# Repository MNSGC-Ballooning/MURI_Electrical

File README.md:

# MURI_Electric
Repository containing EAGLE schematics and PCB files for MURI related payloads

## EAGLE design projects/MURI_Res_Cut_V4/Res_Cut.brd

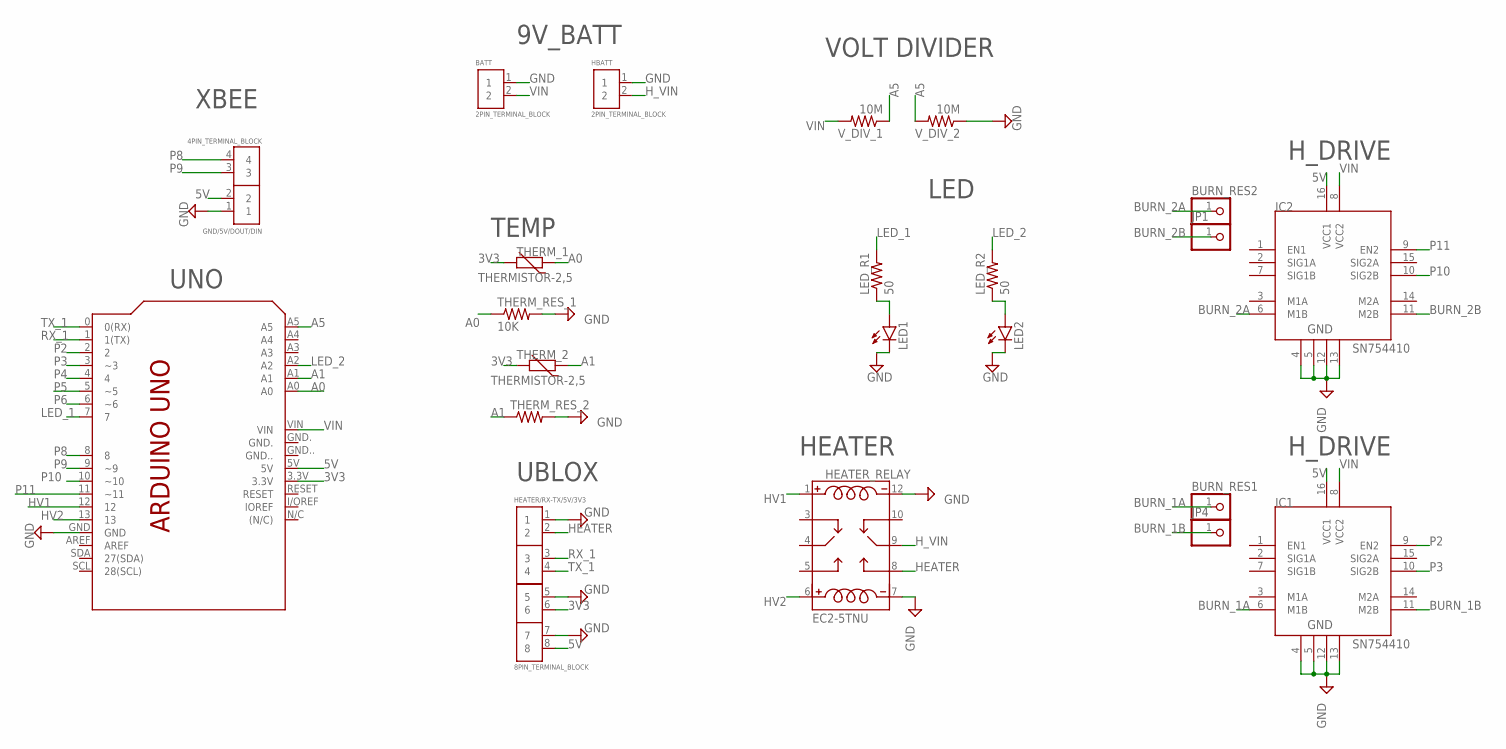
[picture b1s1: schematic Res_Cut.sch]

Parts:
BATT: 2PIN_TERMINAL_BLOCK
BURN_RES1, BURN_RES2: PINHD-1X1CB; 1X01-CLEANBIG
GND/5V/DOUT/DIN: 4PIN_TERMINAL_BLOCK
HBATT: 2PIN_TERMINAL_BLOCK
HEATER/RX-TX/5V/3V3: 8PIN_TERMINAL_BLOCK
HEATER_RELAY: EC2-5TNU; RELAY_EC2-5TNU
IC1, IC2: SN754410; DIP16
JP1, JP4: PINHD-1X1CB; 1X01-CLEANBIG
LED1, LED2: TLLR4400; LED3MM
LED_R1, LED_R2: 50; 0204/7
PCB1: ARDUINO_UNO
THERM_1, THERM_2: THERMISTOR-2,5; RS-2,5
THERM_RES_1, THERM_RES_2: 10K; 0204/7
V_DIV_1, V_DIV_2: 10M; 0204/7

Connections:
3V3: HEATER/RX-TX/5V/3V3.6, PCB1.3.3V, THERM_1.2, THERM_2.2
5V: GND/5V/DOUT/DIN.2, HEATER/RX-TX/5V/3V3.8, IC1.16 (VCC1), IC2.16 (VCC1), PCB1.5V
A0: PCB1.A0, THERM_1.1, THERM_RES_1.1
A1: PCB1.A1, THERM_2.1, THERM_RES_2.1
A5: PCB1.A5, V_DIV_1.1, V_DIV_2.2
BLUE_R2: LED2.A, LED_R2.1
BURN_1A: BURN_RES1.1, IC1.6 (M1B)
BURN_1B: IC1.11 (M2B), JP4.1
BURN_2A: BURN_RES2.1, IC2.6 (M1B)
BURN_2B: IC2.11 (M2B), JP1.1
GND: BATT.1, GND/5V/DOUT/DIN.1, HBATT.1, HEATER/RX-TX/5V/3V3.1, HEATER/RX-TX/5V/3V3.5, HEATER/RX-TX/5V/3V3.7, HEATER_RELAY.7 (C4), HEATER_RELAY.12 (C2), IC1.4, IC1.5, IC1.12, IC1.13, IC2.4, IC2.5, IC2.12, IC2.13, LED1.K (C), LED2.K (C), PCB1.GND, THERM_RES_1.2, THERM_RES_2.2, V_DIV_2.1
HEATER: HEATER/RX-TX/5V/3V3.2, HEATER_RELAY.8 (NO)
HV1: HEATER_RELAY.1 (C1), PCB1.12
HV2: HEATER_RELAY.6 (C3), PCB1.13
H_VIN: HBATT.2, HEATER_RELAY.9 (M)
LED_1: LED_R1.2, PCB1.7
LED_2: LED_R2.2, PCB1.A2
unnamed: LED1.A, LED_R1.1
P2: IC1.9 (EN2), PCB1.2
P3: IC1.10 (SIG2B), PCB1.3 (~3)
P4: PCB1.4
P5: PCB1.5 (~5)
P6: PCB1.6 (~6)
P8: GND/5V/DOUT/DIN.4, PCB1.8
P9: GND/5V/DOUT/DIN.3, PCB1.9 (~9)
P10: IC2.10 (SIG2B), PCB1.10 (~10)
P11: IC2.9 (EN2), PCB1.11 (~11)
RX_1: HEATER/RX-TX/5V/3V3.3, PCB1.1 (1(TX))
TX_1: HEATER/RX-TX/5V/3V3.4, PCB1.0 (0(RX))
VIN: BATT.2, IC1.8 (VCC2), IC2.8 (VCC2), PCB1.VIN, V_DIV_1.2

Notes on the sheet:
TEMP
HEATER
H_DRIVE
UBLOX
XBEE
9V_BATT
UNO
LED
VOLT DIVIDER

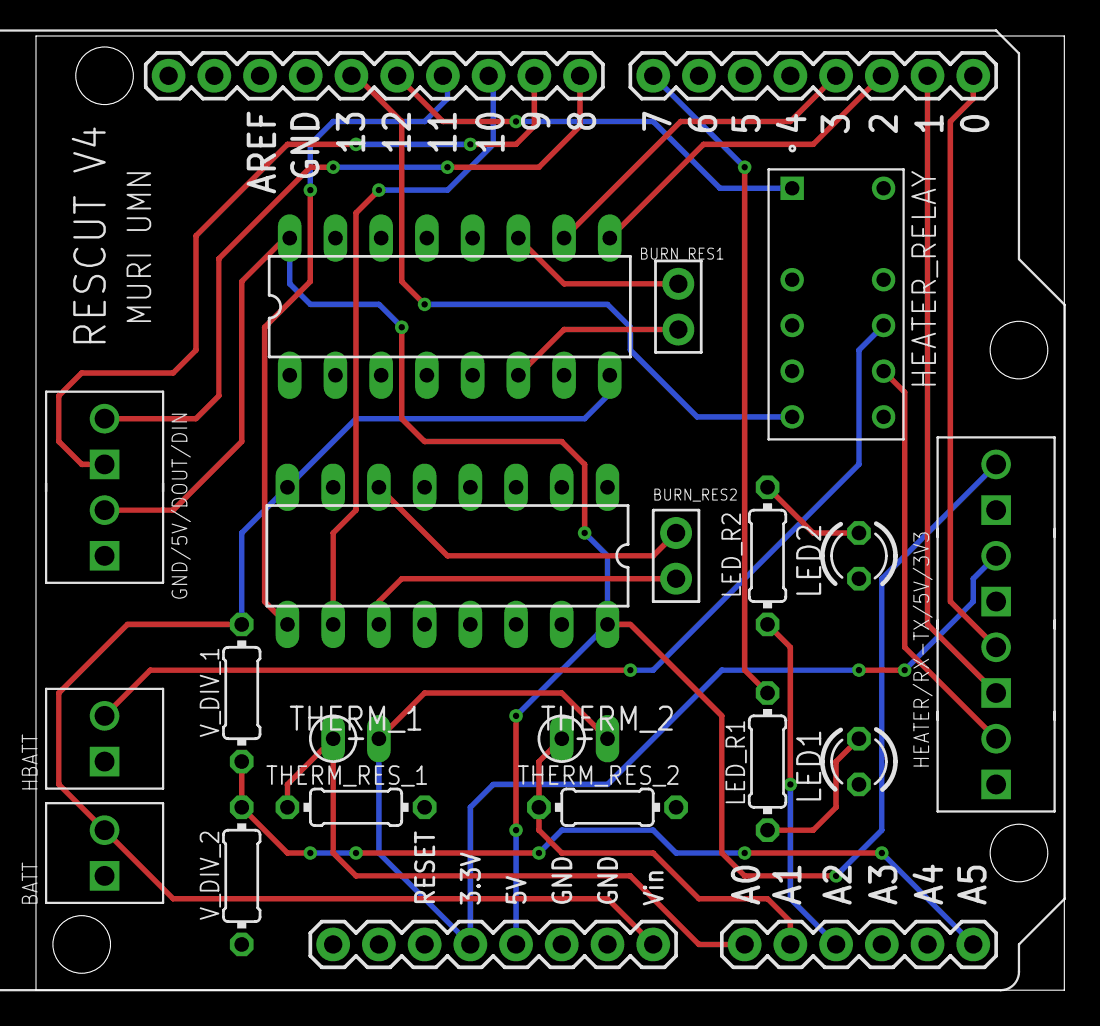
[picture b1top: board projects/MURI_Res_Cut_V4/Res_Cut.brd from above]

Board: 2 copper layers, 57.1 x 53.0 mm, 22 parts (0 on the bottom side), 27 nets.

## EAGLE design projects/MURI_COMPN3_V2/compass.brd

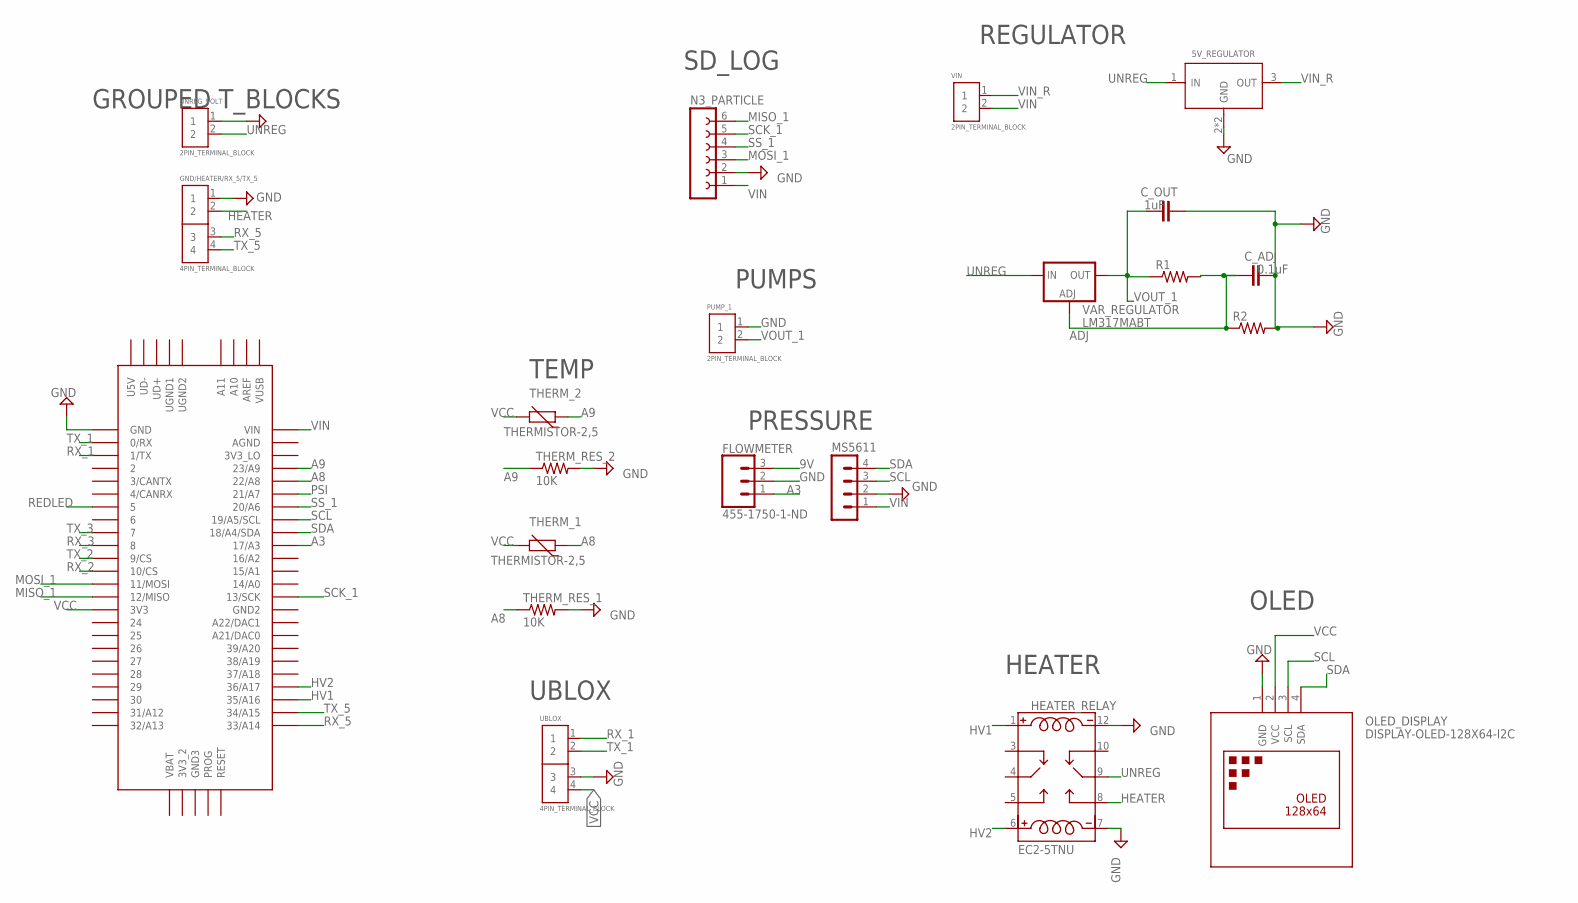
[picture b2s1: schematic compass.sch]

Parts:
5V_REGULATOR: PMIC-L7805CV-DG(TO-220); TO-220
C_ADJ: 0.1uF; C2.5-3
C_OUT: 1uF; C2.5-3
FLOWMETER: 455-1750-1-ND; 1X03
GND/HEATER/RX_5/TX_5: 4PIN_TERMINAL_BLOCK
HEATER_RELAY: EC2-5TNU; RELAY_EC2-5TNU
MS5611: MA04-1
N3_PARTICLE: FE06-1; FE06
OLED_DISPLAY: DISPLAY-OLED-128X64-I2C
PUMP_1: 2PIN_TERMINAL_BLOCK
R1, R2: 0204/7
THERM_1, THERM_2: THERMISTOR-2,5; RS-2,5
THERM_RES_1, THERM_RES_2: 10K; 0204/7
U$1: TEENSY_3.5/3.6
UBLOX: 4PIN_TERMINAL_BLOCK
UNREG_VOLT: 2PIN_TERMINAL_BLOCK
VAR_REGULATOR: LM317MABT; TO220L1
VIN: 2PIN_TERMINAL_BLOCK

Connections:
9V: FLOWMETER.3
A3: FLOWMETER.1, U$1.17/A3
A8: THERM_1.1, THERM_RES_1.1, U$1.22/A8
A9: THERM_2.1, THERM_RES_2.1, U$1.23/A9
ADJ: C_ADJ.2, R1.2, R2.1, VAR_REGULATOR.1 (ADJ)
GND: 5V_REGULATOR.2 (GND), 5V_REGULATOR.HEAT (GND), C_ADJ.1, C_OUT.2, FLOWMETER.2, GND/HEATER/RX_5/TX_5.1, HEATER_RELAY.7 (C4), HEATER_RELAY.12 (C2), MS5611.2, N3_PARTICLE.2, OLED_DISPLAY.1 (GND), PUMP_1.1, R2.2, THERM_RES_1.2, THERM_RES_2.2, U$1.GND, UBLOX.3, UNREG_VOLT.1
HEATER: GND/HEATER/RX_5/TX_5.2, HEATER_RELAY.8 (NO)
HV1: HEATER_RELAY.1 (C1), U$1.35/A16
HV2: HEATER_RELAY.6 (C3), U$1.36/A17
MISO_1: N3_PARTICLE.6, U$1.12/MISO
MOSI_1: N3_PARTICLE.3, U$1.11/MOSI
PSI: U$1.21/A7
REDLED: U$1.5
RX_1: U$1.1/TX, UBLOX.1
RX_2: U$1.10/CS
RX_3: U$1.8
RX_5: GND/HEATER/RX_5/TX_5.3, U$1.33/A14
SCK_1: N3_PARTICLE.5, U$1.13/SCK
SCL: MS5611.3, OLED_DISPLAY.3 (SCL), U$1.19/A5/SCL
SDA: MS5611.4, OLED_DISPLAY.4 (SDA), U$1.18/A4/SDA
SS_1: N3_PARTICLE.4, U$1.20/A6
TX_1: U$1.0/RX, UBLOX.2
TX_2: U$1.9/CS
TX_3: U$1.7
TX_5: GND/HEATER/RX_5/TX_5.4, U$1.34/A15
UNREG: 5V_REGULATOR.1 (IN), HEATER_RELAY.9 (M), UNREG_VOLT.2, VAR_REGULATOR.3 (IN)
VCC: OLED_DISPLAY.2 (VCC), THERM_1.2, THERM_2.2, U$1.3V3, UBLOX.4
VIN: MS5611.1, N3_PARTICLE.1, U$1.VIN, VIN.2
VIN_R: 5V_REGULATOR.3 (OUT), VIN.1
VOUT_1: C_OUT.1, PUMP_1.2, R1.1, VAR_REGULATOR.2 (OUT)

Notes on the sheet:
UBLOX
PRESSURE
OLED
PUMPS
HEATER
REGULATOR
SD_LOG
TEMP
GROUPED T_BLOCKS

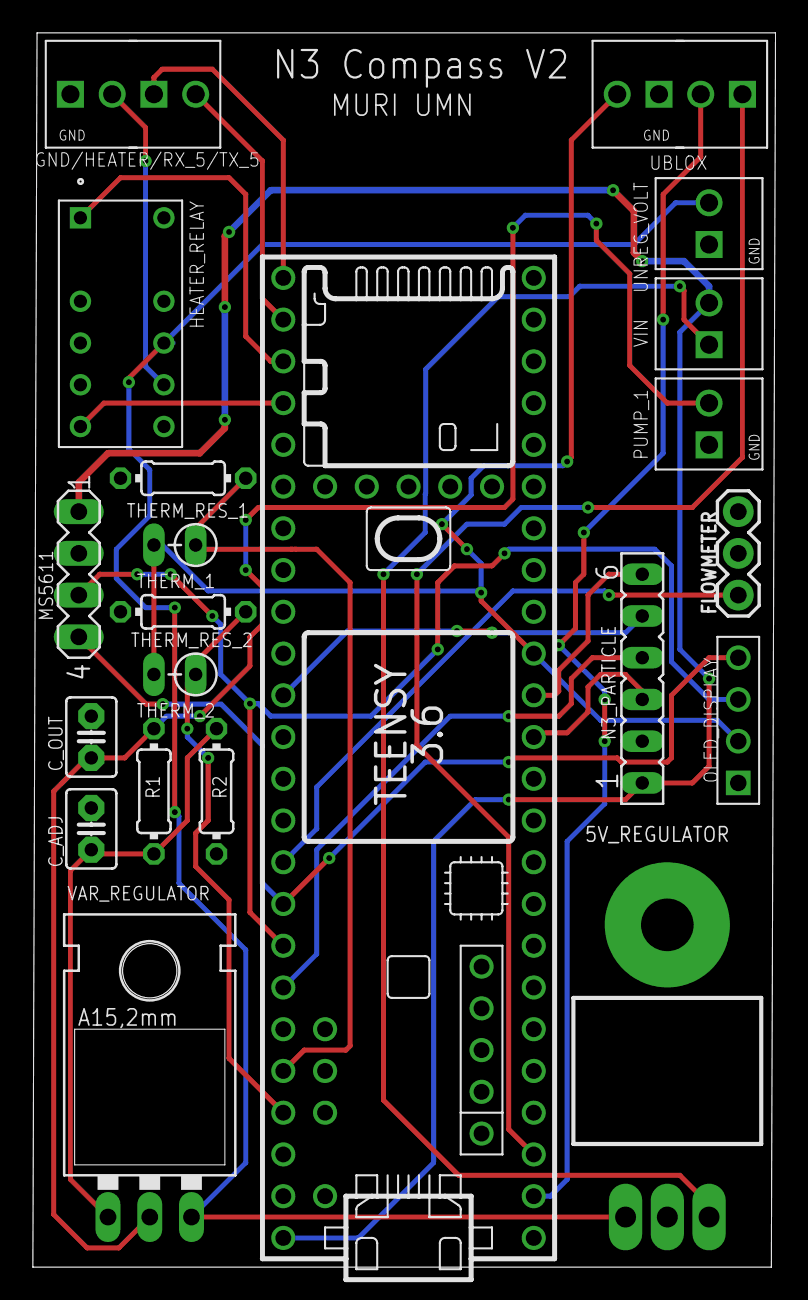
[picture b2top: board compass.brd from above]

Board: 2 copper layers, 45.2 x 75.1 mm, 21 parts (0 on the bottom side), 23 nets.

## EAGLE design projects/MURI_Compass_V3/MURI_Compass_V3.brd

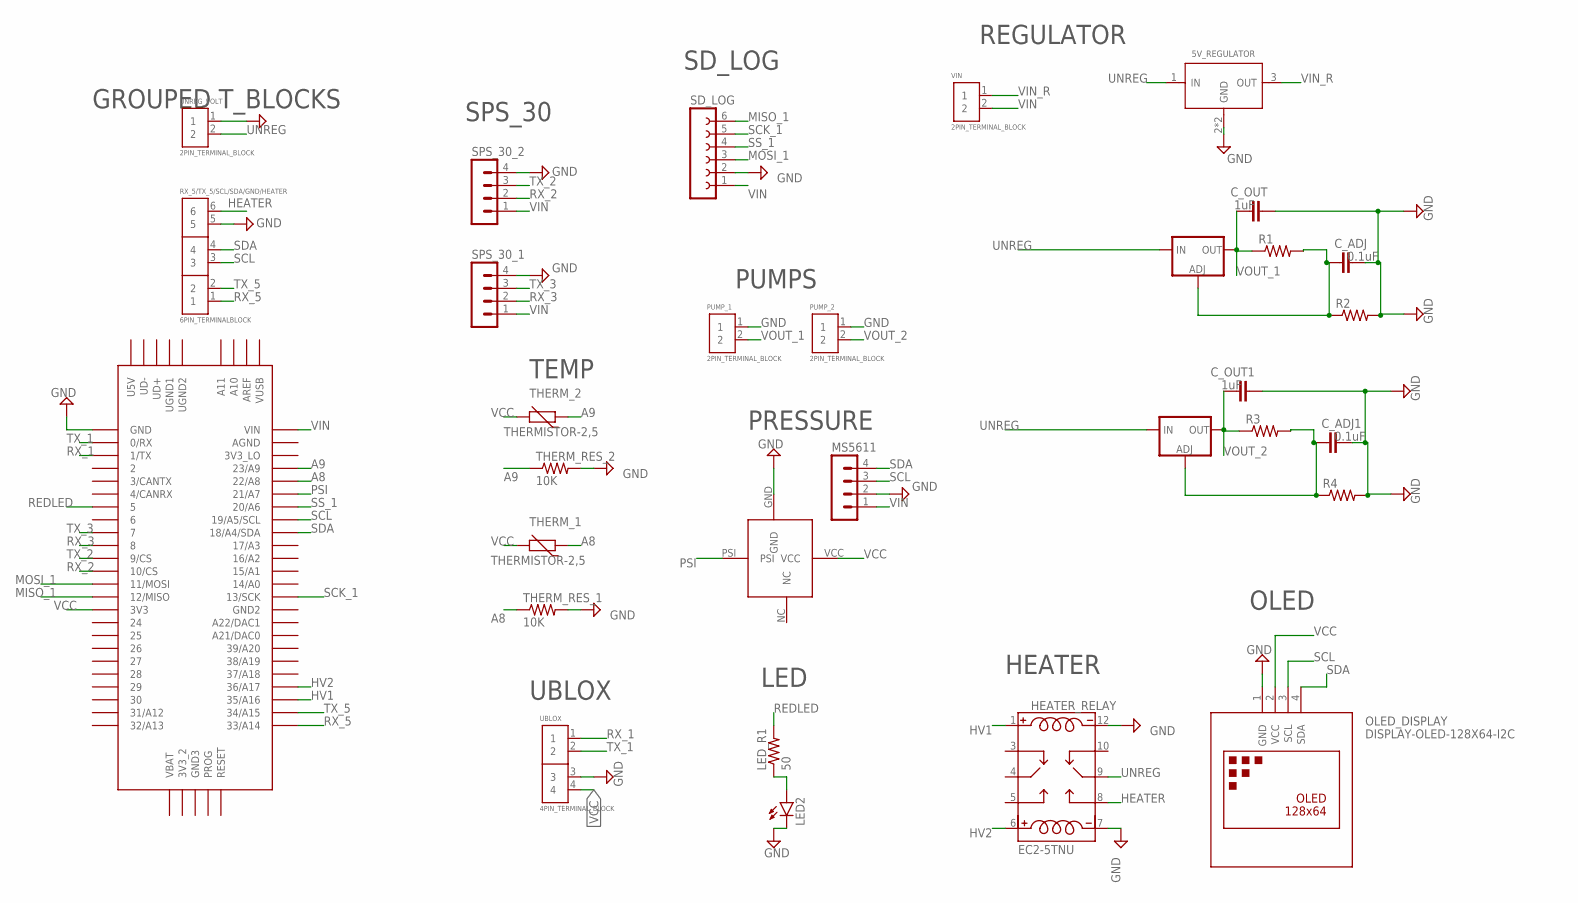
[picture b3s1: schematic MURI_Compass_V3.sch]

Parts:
5V_REGULATOR: PMIC-L7805CV-DG(TO-220); TO-220
C_ADJ, C_ADJ1: 0.1uF; C2.5-3
C_OUT, C_OUT1: 1uF; C2.5-3
HEATER_RELAY: EC2-5TNU; RELAY_EC2-5TNU
LED2: TLLR4400; LED3MM
LED_R1: 50; 0204/7
MS5611: MA04-1
OLED_DISPLAY: DISPLAY-OLED-128X64-I2C
PRESSURE_SENSOR: SSCSANN015PAAA5
PUMP_1, PUMP_2: 2PIN_TERMINAL_BLOCK
R1, R2, R3, R4: 0204/7
RX_5/TX_5/SCL/SDA/GND/HEATER: 6PIN_TERMINALBLOCK
SD_LOG: FE06-1; FE06
SPS_30_1, SPS_30_2: MA04-1
THERM_1, THERM_2: THERMISTOR-2,5; RS-2,5
THERM_RES_1, THERM_RES_2: 10K; 0204/7
U1, U2: V_REG_317SINK; TO220-ADJ
U$1: TEENSY_3.5/3.6
UBLOX: 4PIN_TERMINAL_BLOCK
UNREG_VOLT: 2PIN_TERMINAL_BLOCK
VIN: 2PIN_TERMINAL_BLOCK

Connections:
A8: THERM_1.1, THERM_RES_1.1, U$1.22/A8
A9: THERM_2.1, THERM_RES_2.1, U$1.23/A9
GND: 5V_REGULATOR.2 (GND), 5V_REGULATOR.HEAT (GND), C_ADJ.1, C_ADJ1.1, C_OUT.2, C_OUT1.2, HEATER_RELAY.7 (C4), HEATER_RELAY.12 (C2), LED2.K (C), MS5611.2, OLED_DISPLAY.1 (GND), PRESSURE_SENSOR.GND, PUMP_1.1, PUMP_2.1, R2.2, R4.2, RX_5/TX_5/SCL/SDA/GND/HEATER.5, SD_LOG.2, SPS_30_1.4, SPS_30_2.4, THERM_RES_1.2, THERM_RES_2.2, U$1.GND, UBLOX.3, UNREG_VOLT.1
HEATER: HEATER_RELAY.8 (NO), RX_5/TX_5/SCL/SDA/GND/HEATER.6
HV1: HEATER_RELAY.1 (C1), U$1.35/A16
HV2: HEATER_RELAY.6 (C3), U$1.36/A17
MISO_1: SD_LOG.6, U$1.12/MISO
MOSI_1: SD_LOG.3, U$1.11/MOSI
unnamed: C_ADJ1.2, R3.2, R4.1, U2.ADJ
unnamed: LED2.A, LED_R1.1
unnamed: C_ADJ.2, R1.2, R2.1, U1.ADJ
PSI: PRESSURE_SENSOR.PSI, U$1.21/A7
REDLED: LED_R1.2, U$1.5
RX_1: U$1.1/TX, UBLOX.1
RX_2: SPS_30_2.2, U$1.10/CS
RX_3: SPS_30_1.2, U$1.8
RX_5: RX_5/TX_5/SCL/SDA/GND/HEATER.1, U$1.33/A14
SCK_1: SD_LOG.5, U$1.13/SCK
SCL: MS5611.3, OLED_DISPLAY.3 (SCL), RX_5/TX_5/SCL/SDA/GND/HEATER.3, U$1.19/A5/SCL
SDA: MS5611.4, OLED_DISPLAY.4 (SDA), RX_5/TX_5/SCL/SDA/GND/HEATER.4, U$1.18/A4/SDA
SS_1: SD_LOG.4, U$1.20/A6
TX_1: U$1.0/RX, UBLOX.2
TX_2: SPS_30_2.3, U$1.9/CS
TX_3: SPS_30_1.3, U$1.7
TX_5: RX_5/TX_5/SCL/SDA/GND/HEATER.2, U$1.34/A15
UNREG: 5V_REGULATOR.1 (IN), HEATER_RELAY.9 (M), U1.IN, U2.IN, UNREG_VOLT.2
VCC: OLED_DISPLAY.2 (VCC), PRESSURE_SENSOR.VCC, THERM_1.2, THERM_2.2, U$1.3V3, UBLOX.4
VIN: MS5611.1, SD_LOG.1, SPS_30_1.1, SPS_30_2.1, U$1.VIN, VIN.2
VIN_R: 5V_REGULATOR.3 (OUT), VIN.1
VOUT_1: C_OUT.1, PUMP_1.2, R1.1, U1.OUT
VOUT_2: C_OUT1.1, PUMP_2.2, R3.1, U2.OUT

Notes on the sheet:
UBLOX
LED
PRESSURE
OLED
PUMPS
HEATER
REGULATOR
SD_LOG
SPS_30
TEMP
GROUPED T_BLOCKS

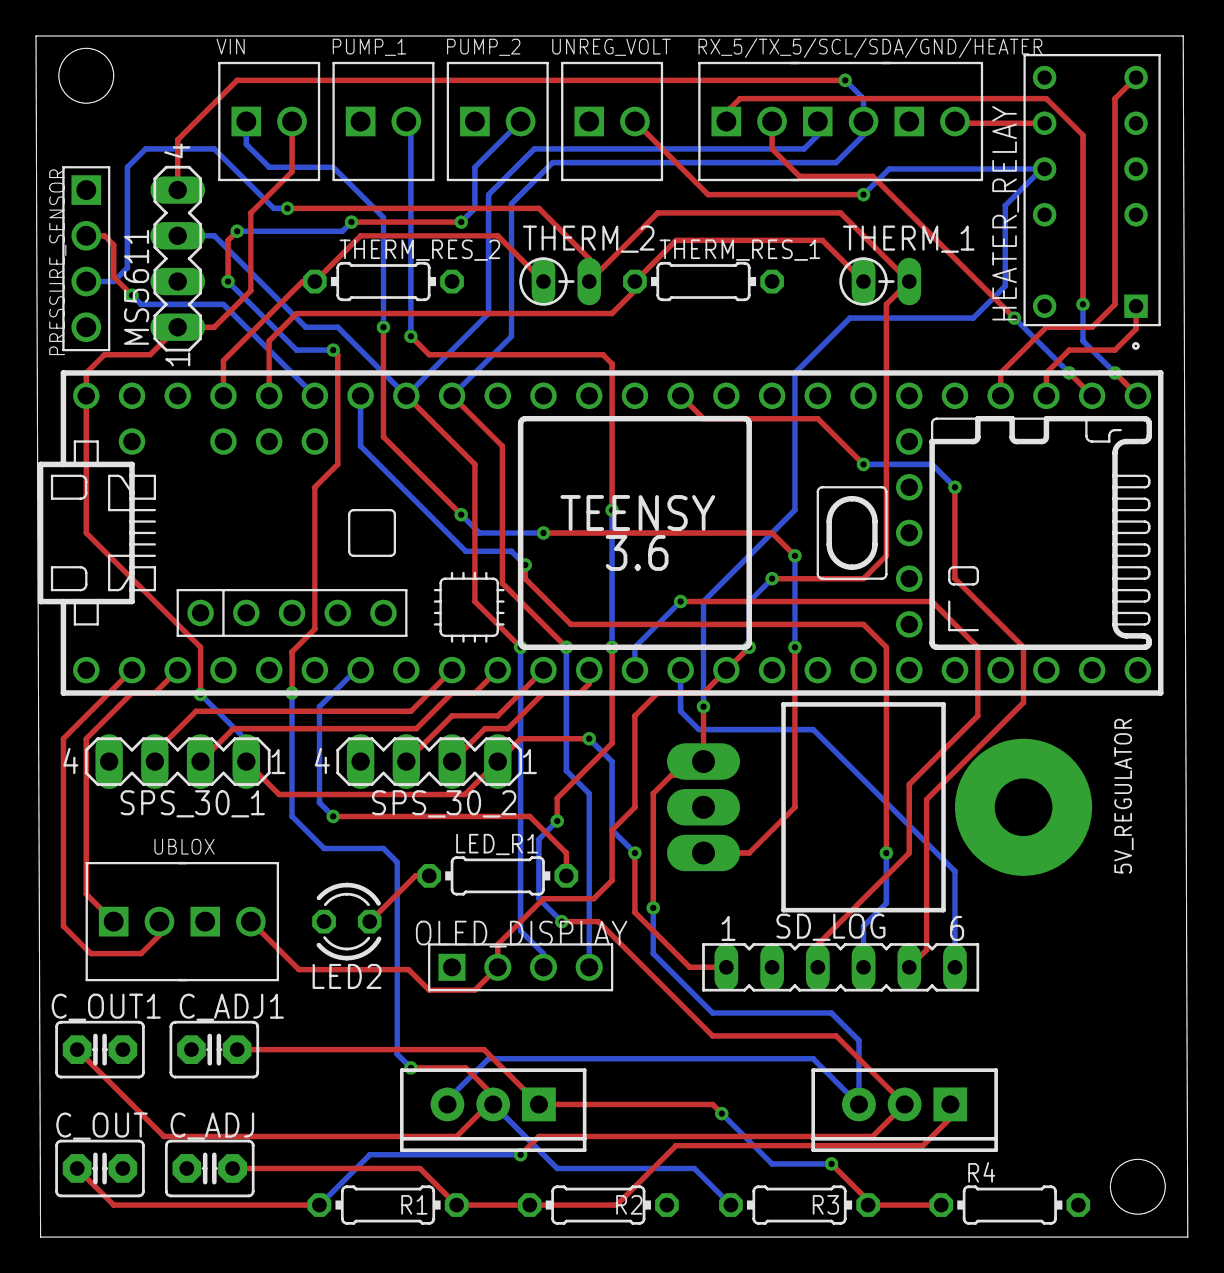
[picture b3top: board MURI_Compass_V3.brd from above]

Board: 2 copper layers, 64.0 x 66.7 mm, 31 parts (0 on the bottom side), 31 nets.

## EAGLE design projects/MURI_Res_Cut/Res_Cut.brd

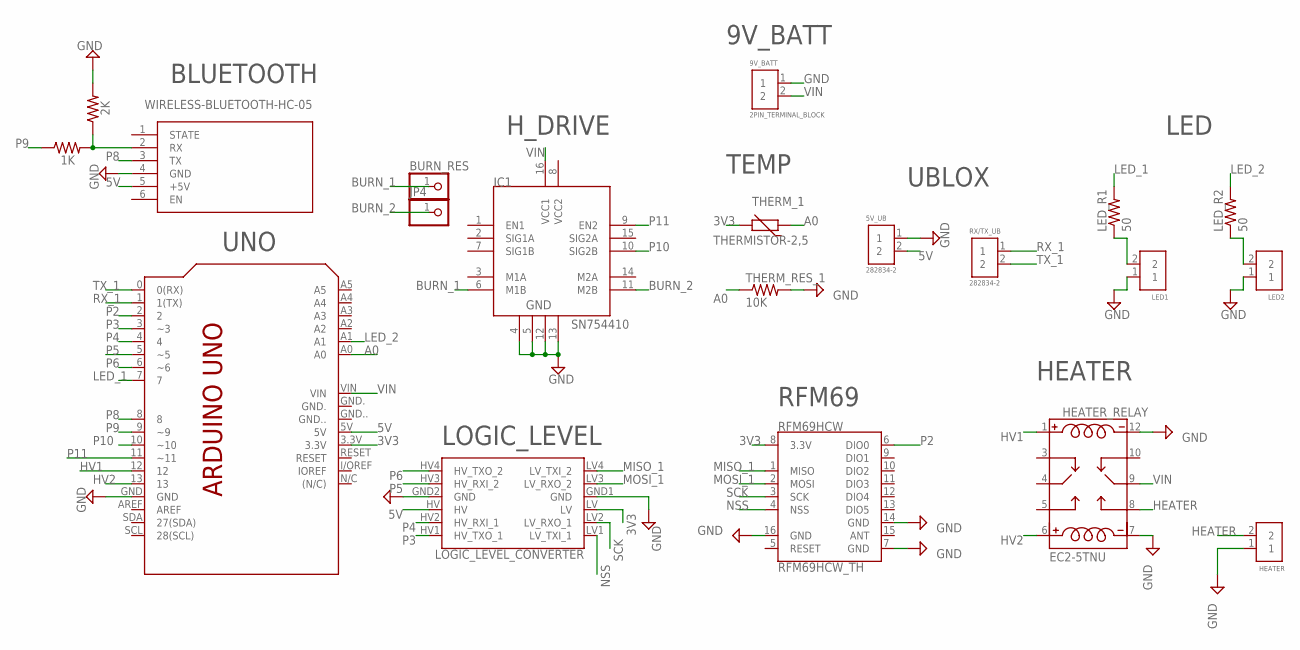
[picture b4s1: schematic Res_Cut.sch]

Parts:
5V_UB: 282834-2; CONN_282834-2
9V_BATT: 2PIN_TERMINAL_BLOCK
BLUE_R1: 1K; 0204/7
BLUE_R2: 2K; 0204/7
BURN_RES: PINHD-1X1CB; 1X01-CLEANBIG
HEATER: 2PIN_TERMINAL_BLOCK
HEATER_RELAY: EC2-5TNU; RELAY_EC2-5TNU
IC1: SN754410; DIP16
JP4: PINHD-1X1CB; 1X01-CLEANBIG
LED1, LED2: 282834-2; CONN_282834-2
LED_R1, LED_R2: 50; 0204/7
LOGIC_LEVEL_CONVERTER: SPARKFUN_LOGIC_LEVEL_CONVERTER
PCB1: ARDUINO_UNO
RFM69HCW: RFM69HCW_TH; RFM69HCW
RX/TX_UB: 282834-2; CONN_282834-2
THERM_1: THERMISTOR-2,5; RS-2,5
THERM_RES_1: 10K; 0204/7
U$1: WIRELESS-BLUETOOTH-HC-05

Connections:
3V3: LOGIC_LEVEL_CONVERTER.LV, PCB1.3.3V, RFM69HCW.8 (3.3V), THERM_1.2
5V: 5V_UB.2, LOGIC_LEVEL_CONVERTER.HV, PCB1.5V, U$1.5 (+5V)
A0: PCB1.A0, THERM_1.1, THERM_RES_1.1
BLUE_R2: LED2.2, LED_R2.1
BURN_1: BURN_RES.1, IC1.6 (M1B)
BURN_2: IC1.11 (M2B), JP4.1
GND: 5V_UB.1, 9V_BATT.1, BLUE_R2.2, HEATER.1, HEATER_RELAY.7 (C4), HEATER_RELAY.12 (C2), IC1.4, IC1.5, IC1.12, IC1.13, LED1.1, LED2.1, LOGIC_LEVEL_CONVERTER.GND1 (GND), LOGIC_LEVEL_CONVERTER.GND2 (GND), PCB1.GND, RFM69HCW.7 (GND), RFM69HCW.16 (GND), THERM_RES_1.2, U$1.4 (GND)
HEATER: HEATER.2, HEATER_RELAY.8 (NO)
HV1: HEATER_RELAY.1 (C1), PCB1.12
HV2: HEATER_RELAY.6 (C3), PCB1.13
LED_1: LED_R1.2, PCB1.7
LED_2: LED_R2.2, PCB1.A1
MISO_1: LOGIC_LEVEL_CONVERTER.LV4 (LV_TXI_2), RFM69HCW.1 (MISO)
MOSI_1: LOGIC_LEVEL_CONVERTER.LV3 (LV_RXO_2), RFM69HCW.2 (MOSI)
unnamed: BLUE_R1.2, BLUE_R2.1, U$1.2 (RX)
unnamed: LED1.2, LED_R1.1
NSS: LOGIC_LEVEL_CONVERTER.LV1 (LV_TXI_1), RFM69HCW.4 (NSS)
P2: PCB1.2, RFM69HCW.6 (DIO0)
P3: LOGIC_LEVEL_CONVERTER.HV1 (HV_TXO_1), PCB1.3 (~3)
P4: LOGIC_LEVEL_CONVERTER.HV2 (HV_RXI_1), PCB1.4
P5: LOGIC_LEVEL_CONVERTER.HV3 (HV_RXI_2), PCB1.5 (~5)
P6: LOGIC_LEVEL_CONVERTER.HV4 (HV_TXO_2), PCB1.6 (~6)
P8: PCB1.8, U$1.3 (TX)
P9: BLUE_R1.1, PCB1.9 (~9)
P10: IC1.10 (SIG2B), PCB1.10 (~10)
P11: IC1.9 (EN2), PCB1.11 (~11)
RX_1: PCB1.1 (1(TX)), RX/TX_UB.1
SCK: LOGIC_LEVEL_CONVERTER.LV2 (LV_RXO_1), RFM69HCW.3 (SCK)
TX_1: PCB1.0 (0(RX)), RX/TX_UB.2
VCC2: IC1.8 (VCC2)
VIN: 9V_BATT.2, HEATER_RELAY.9 (M), IC1.16 (VCC1), PCB1.VIN

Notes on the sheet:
TEMP
HEATER
H_DRIVE
UBLOX
LOGIC_LEVEL
BLUETOOTH
RFM69
9V_BATT
UNO
LED

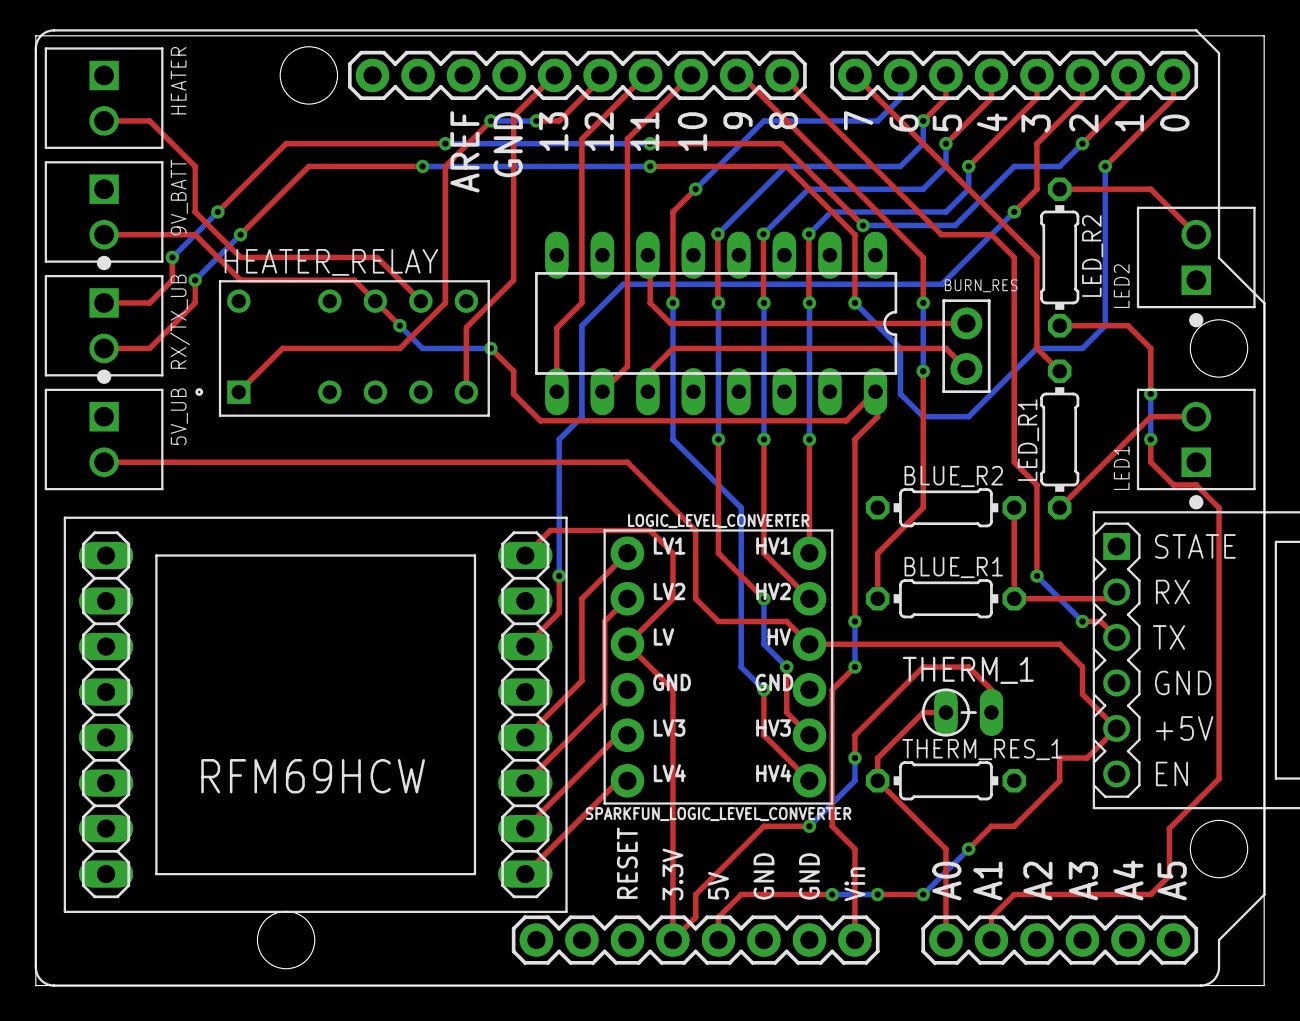
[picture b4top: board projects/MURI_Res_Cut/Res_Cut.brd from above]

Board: 2 copper layers, 68.6 x 53.0 mm, 20 parts (0 on the bottom side), 30 nets.

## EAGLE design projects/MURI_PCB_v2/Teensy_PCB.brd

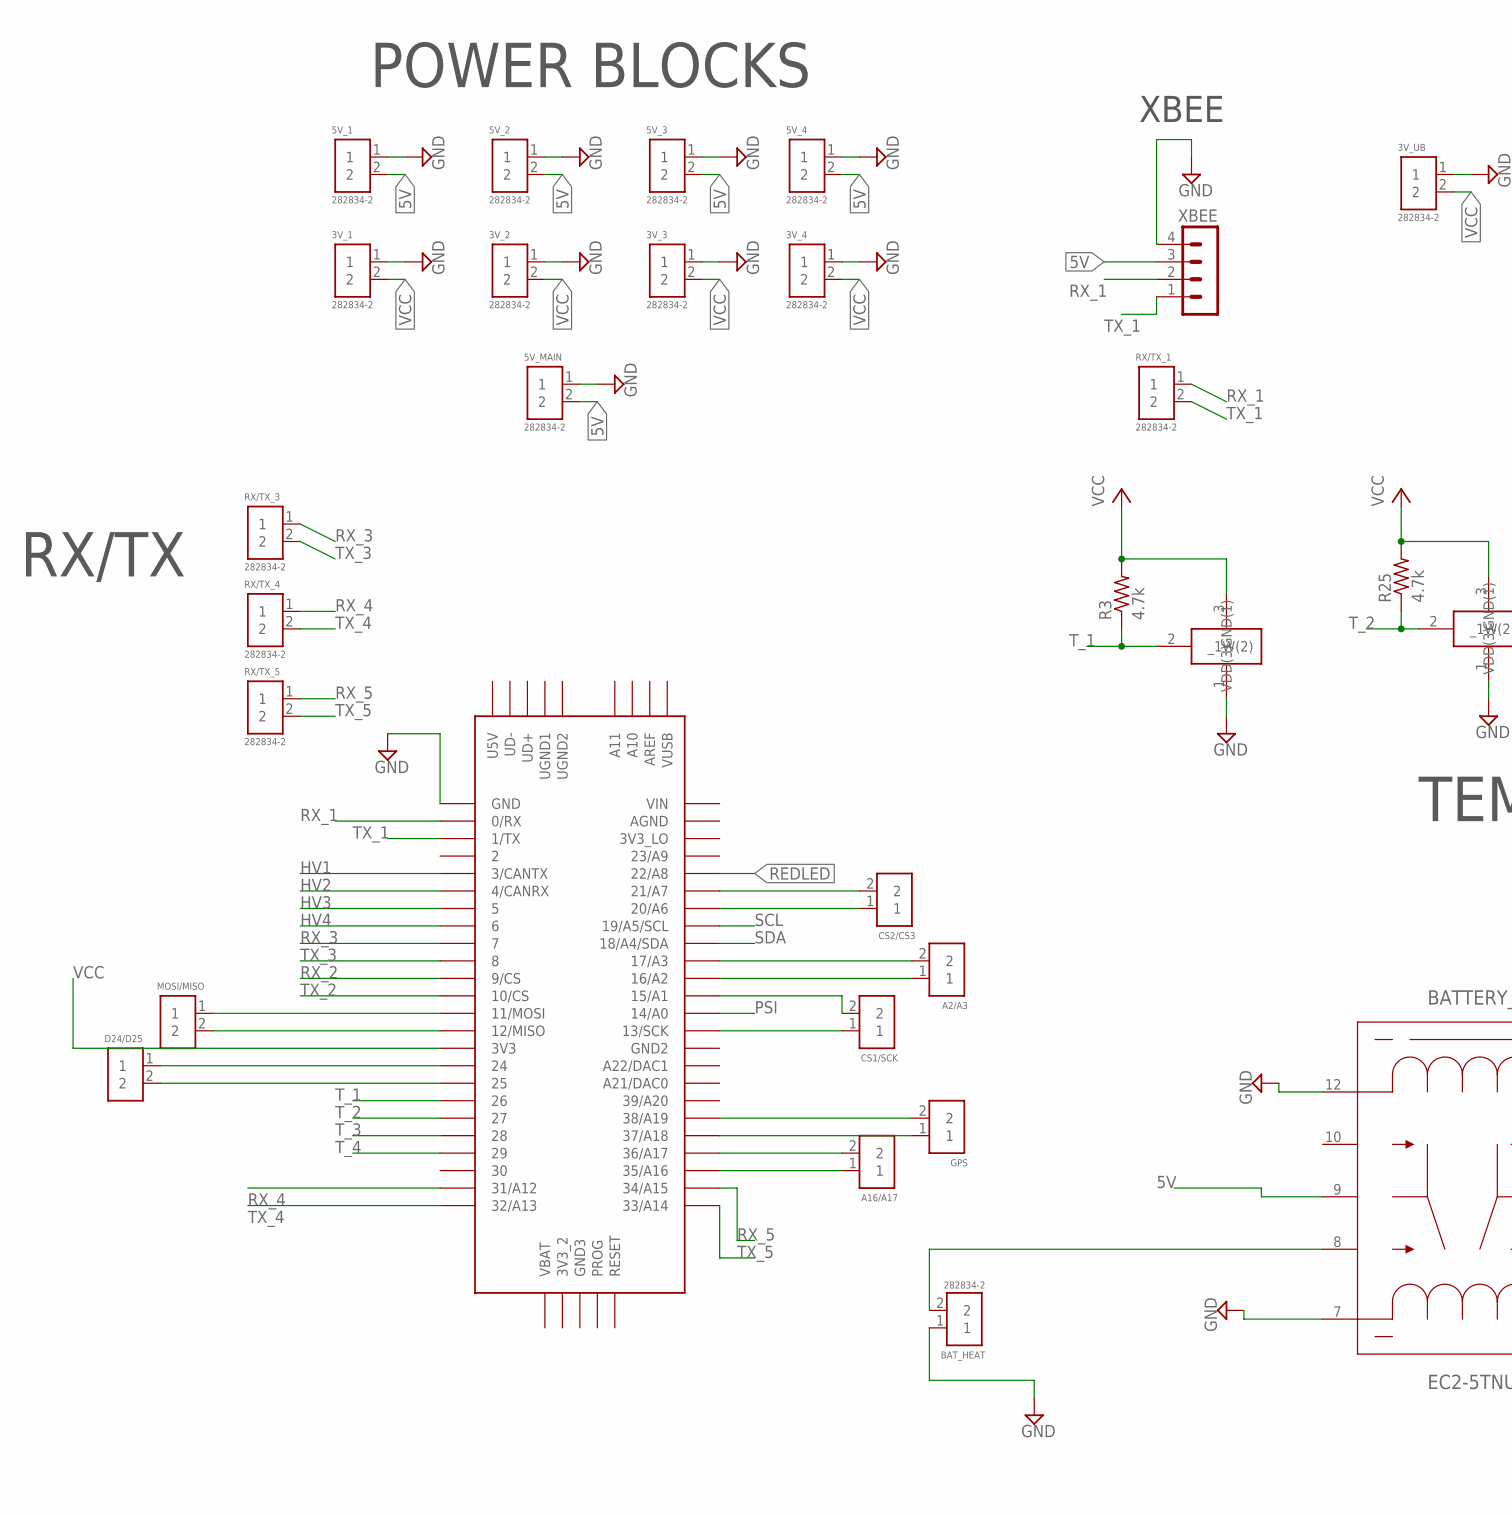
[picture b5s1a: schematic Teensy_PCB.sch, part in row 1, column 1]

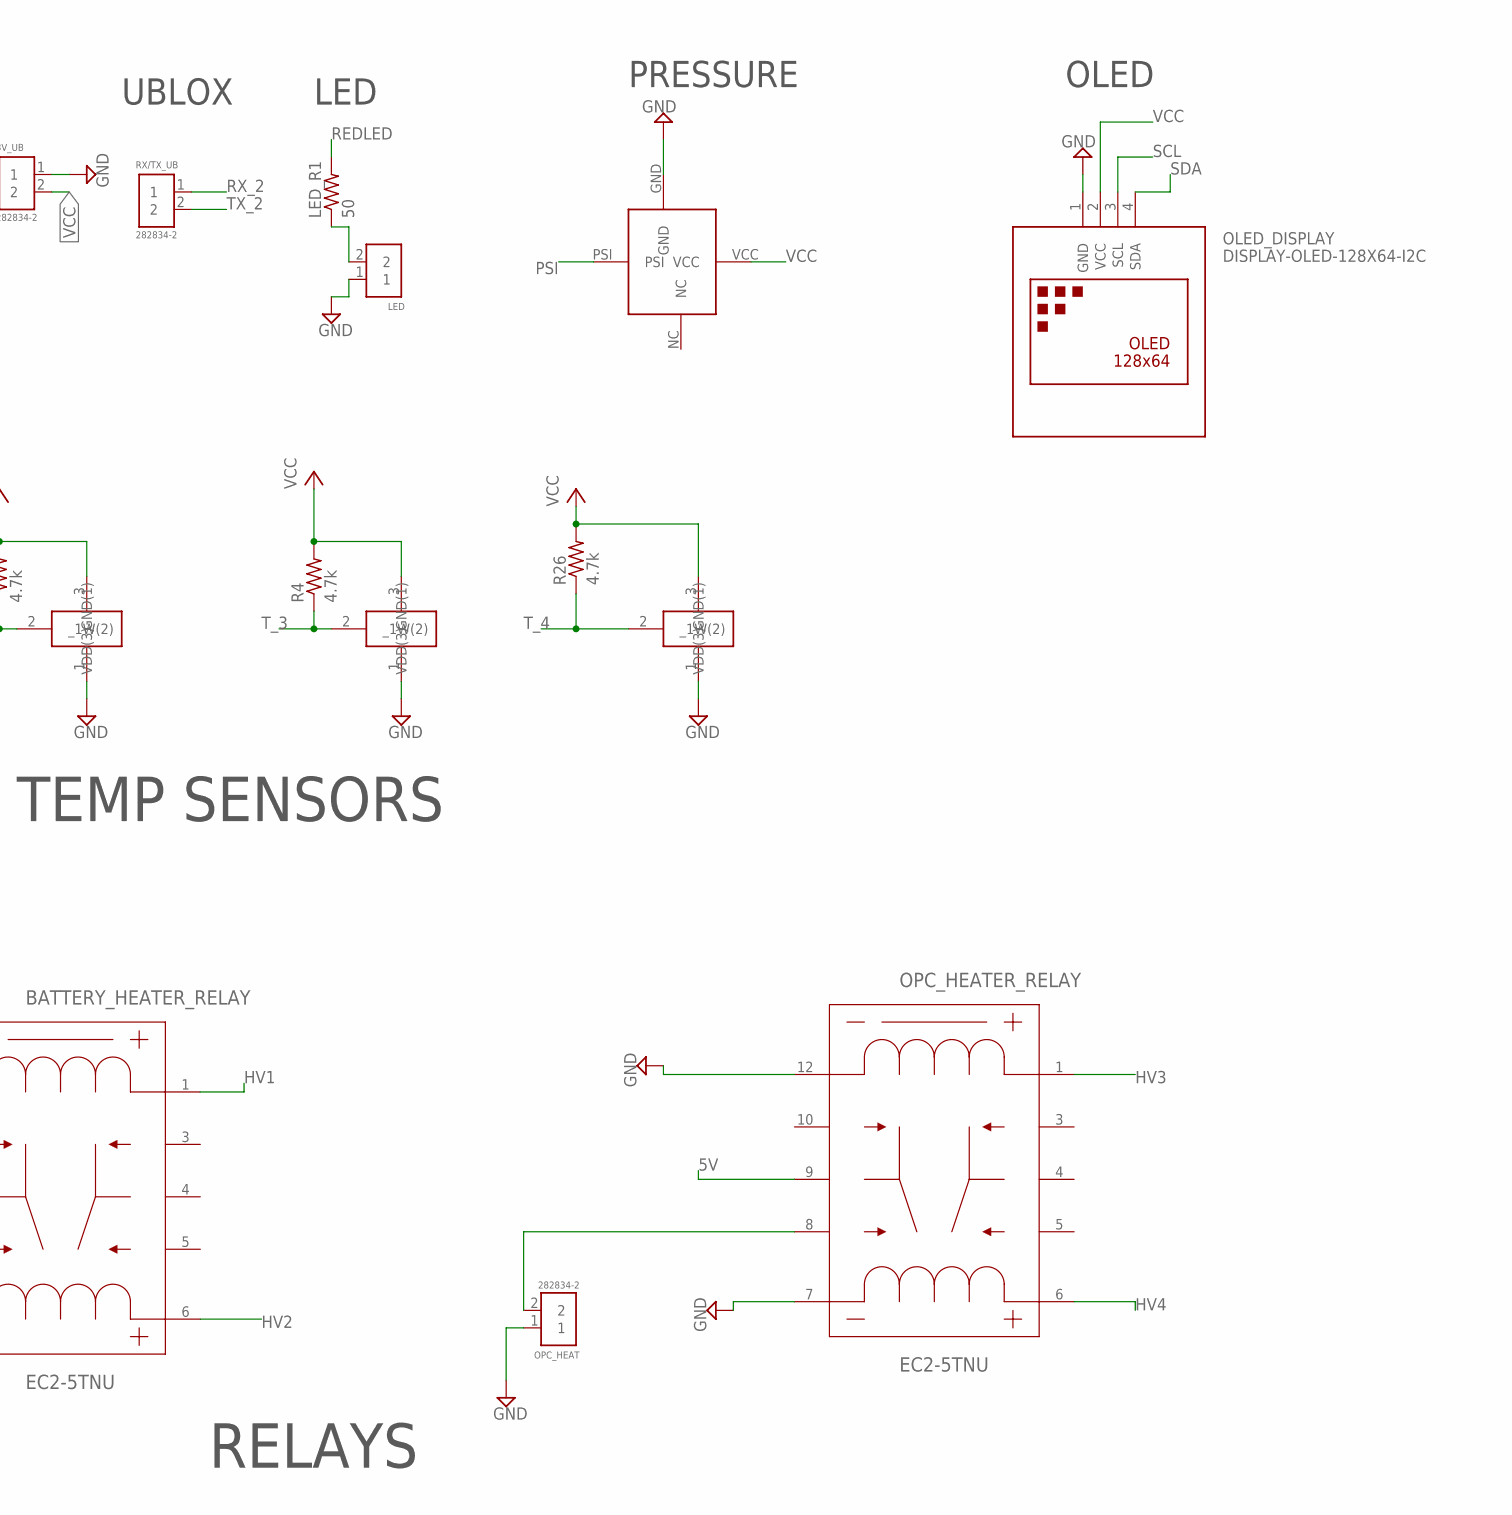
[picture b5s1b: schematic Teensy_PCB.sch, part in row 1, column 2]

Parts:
3V_1, 3V_2, 3V_3, 3V_4, 3V_UB, 5V_1, 5V_2, 5V_3, 5V_4, 5V_MAIN: 282834-2; CONN_282834-2
A2/A3, A16/A17: 282834-2; CONN_282834-2
BATTERY_HEATER_RELAY: EC2-5TNU; EC2TNU
BAT_HEAT: 282834-2; CONN_282834-2
CS1/SCK, CS2/CS3: 282834-2; CONN_282834-2
D24/D25: 282834-2; CONN_282834-2
GPS: 282834-2; CONN_282834-2
LED: 282834-2; CONN_282834-2
LED_R1: 50; 0204/7
MOSI/MISO: 282834-2; CONN_282834-2
OLED_DISPLAY: DISPLAY-OLED-128X64-I2C
OPC_HEAT: 282834-2; CONN_282834-2
OPC_HEATER_RELAY: EC2-5TNU; EC2TNU
PRESSURE_SENSOR: SSCSANN015PAAA5
R3, R4, R25, R26: 4.7k; 0204/7
RX/TX_1, RX/TX_3, RX/TX_4, RX/TX_5: 282834-2; CONN_282834-2
RX/TX_UB: 282834-2; CONN_282834-2
TEMP_1, TEMP_2, TEMP_3, TEMP_4: DS18B20.2; TO92-
U$1: TEENSY_3.5/3.6
XBEE: MA04-1

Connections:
5V: 5V_1.2, 5V_2.2, 5V_3.2, 5V_4.2, 5V_MAIN.2, BATTERY_HEATER_RELAY.9 (8), OPC_HEATER_RELAY.9 (8), XBEE.3
GND: 3V_1.1, 3V_2.1, 3V_3.1, 3V_4.1, 3V_UB.1, 5V_1.1, 5V_2.1, 5V_3.1, 5V_4.1, 5V_MAIN.1, BATTERY_HEATER_RELAY.7 (6), BATTERY_HEATER_RELAY.12 (10), BAT_HEAT.1, LED.1, OLED_DISPLAY.1 (GND), OPC_HEAT.1, OPC_HEATER_RELAY.7 (6), OPC_HEATER_RELAY.12 (10), PRESSURE_SENSOR.GND, TEMP_1.1 (GND(1)), TEMP_2.1 (GND(1)), TEMP_3.1 (GND(1)), TEMP_4.1 (GND(1)), U$1.GND, XBEE.4
HV1: BATTERY_HEATER_RELAY.1, U$1.3/CANTX
HV2: BATTERY_HEATER_RELAY.6 (5), U$1.4/CANRX
HV3: OPC_HEATER_RELAY.1, U$1.5
HV4: OPC_HEATER_RELAY.6 (5), U$1.6
unnamed: OPC_HEAT.2, OPC_HEATER_RELAY.8 (7)
unnamed: BATTERY_HEATER_RELAY.8 (7), BAT_HEAT.2
unnamed: MOSI/MISO.1, U$1.11/MOSI
unnamed: LED.2, LED_R1.1
unnamed: MOSI/MISO.2, U$1.12/MISO
unnamed: CS1/SCK.2, U$1.15/A1
unnamed: A2/A3.2, U$1.17/A3
unnamed: CS1/SCK.1, U$1.13/SCK
unnamed: A2/A3.1, U$1.16/A2
unnamed: CS2/CS3.2, U$1.21/A7
unnamed: CS2/CS3.1, U$1.20/A6
unnamed: D24/D25.1, U$1.24
unnamed: D24/D25.2, U$1.25
unnamed: A16/A17.1, U$1.35/A16
unnamed: A16/A17.2, U$1.36/A17
unnamed: GPS.1, U$1.37/A18
unnamed: GPS.2, U$1.38/A19
PSI: PRESSURE_SENSOR.PSI, U$1.14/A0
REDLED: LED_R1.2, U$1.22/A8
RX_1: RX/TX_1.1, U$1.0/RX, XBEE.2
RX_2: RX/TX_UB.1, U$1.9/CS
RX_3: RX/TX_3.1, U$1.7
RX_4: RX/TX_4.1, U$1.31/A12
RX_5: RX/TX_5.1, U$1.34/A15
SCL: OLED_DISPLAY.3 (SCL), U$1.19/A5/SCL
SDA: OLED_DISPLAY.4 (SDA), U$1.18/A4/SDA
TX_1: RX/TX_1.2, U$1.1/TX, XBEE.1
TX_2: RX/TX_UB.2, U$1.10/CS
TX_3: RX/TX_3.2, U$1.8
TX_4: RX/TX_4.2, U$1.32/A13
TX_5: RX/TX_5.2, U$1.33/A14
T_1: R3.1, TEMP_1.2 (_1W(2)), U$1.26
T_2: R25.1, TEMP_2.2 (_1W(2)), U$1.27
T_3: R4.1, TEMP_3.2 (_1W(2)), U$1.28
T_4: R26.1, TEMP_4.2 (_1W(2)), U$1.29
VCC: 3V_1.2, 3V_2.2, 3V_3.2, 3V_4.2, 3V_UB.2, OLED_DISPLAY.2 (VCC), PRESSURE_SENSOR.VCC, R3.2, R4.2, R25.2, R26.2, TEMP_1.3 (VDD(3)), TEMP_2.3 (VDD(3)), TEMP_3.3 (VDD(3)), TEMP_4.3 (VDD(3)), U$1.3V3

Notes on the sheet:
RX/TX
TEMP SENSORS
RELAYS
POWER BLOCKS
XBEE
UBLOX
LED
PRESSURE
OLED

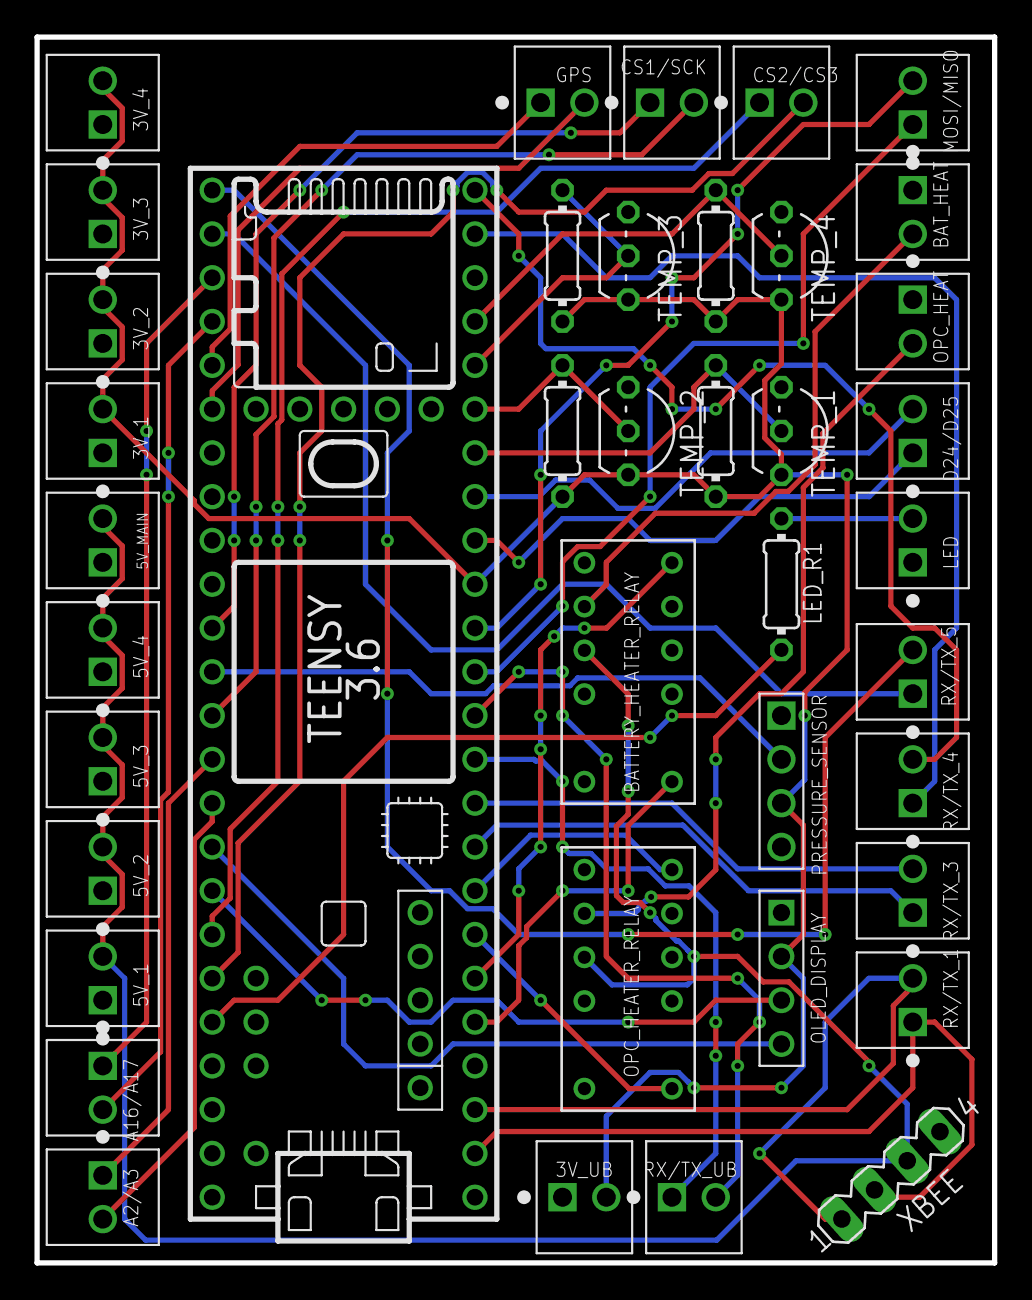
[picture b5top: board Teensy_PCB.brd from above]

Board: 2 copper layers, 55.5 x 71.1 mm, 40 parts (0 on the bottom side), 42 nets.

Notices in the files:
parts and their libraries:
diy-modules: Released under the Creative Commons Attribution 4.0 International License: http://creativecommons.org/licenses/by/4.0
SparkFun-Connectors: Licensing: Creative Commons ShareAlike 4.0 International - https://creativecommons.org/licenses/by-sa/4.0
